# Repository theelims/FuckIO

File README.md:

# FuckIO
An opensource fucking machine, that is far superiour to anything on the market.

## Specs
* Easy to built just with a 3D-printer, screwdrivers and easy-to-source parts.
* Completely 3D-printable with easy to print parts and almost no supports. Also avoiding tight tolerances to make this accessable as possible. 
* Simple, yet verastile mechanics.
* Based on a linear position drive, not a crank mechanism.
* An 24V PWM output to drive external systems. Could be lube pumps, vibrators, etc.

## Mechanics
The mechanics is a direct derivative of an other open source project called OSSM. You can also find some informations about this build on their Discord.
https://github.com/KinkyMakers/OSSM-hardware

The motor mount is designed for a NEMA23 servo or stepper motor. Any motor fitting to this standart should work. 

### BOM
* iHSV57-30-18-36-... integrated servo motor from JMC
* 24V Power Brick Mean Well GST280A24-C6P 
* 40cm MGN12H linear rail
* 4x 605-2RS Z2 bearings
* Micro Switch
* GT2 20 Tooth Pulley for 8mm Axis and a 10mm belt
* GT2 belt with 10mm width
* Various M3 and M5 screws and nuts
* OSSM Ref Board from Research and Desire: https://shop.researchanddesire.com/collections/all/products/ossm-reference-board
* M5 Stack Remote Control from Ortlof: https://github.com/ortlof/OSSM-M5-Remote

## Control
### Firmware
The currently best firmware is the official OSSM firmware, or Ortlof's firmware for the M5 Remote https://github.com/ortlof/OSSM-M5-Remote

The firmware in the repository can only be used in conjunction with node-red.

The firmware uses the following projects:
* IotWebConf for WiFi provisioning: https://github.com/prampec/IotWebConf. Check the [end-user manual](https://github.com/prampec/IotWebConf/blob/master/doc/UsersManual.md) on how to use it.
* MQTT for communication: https://github.com/256dpi/arduino-mqtt Albeit SSL is not supported.
* My own library for generating the stroking motion: https://github.com/theelims/StrokeEngine/
* Which in turn uses https://github.com/gin66/FastAccelStepper for step generation and interfacing the servo motor.

### node-red
I've setup a node-red instance on my NAS to control FuckIO through MQTT messages. Have a look at the provided [flows.json](node-red/flows.json) to draw some inspiration from.

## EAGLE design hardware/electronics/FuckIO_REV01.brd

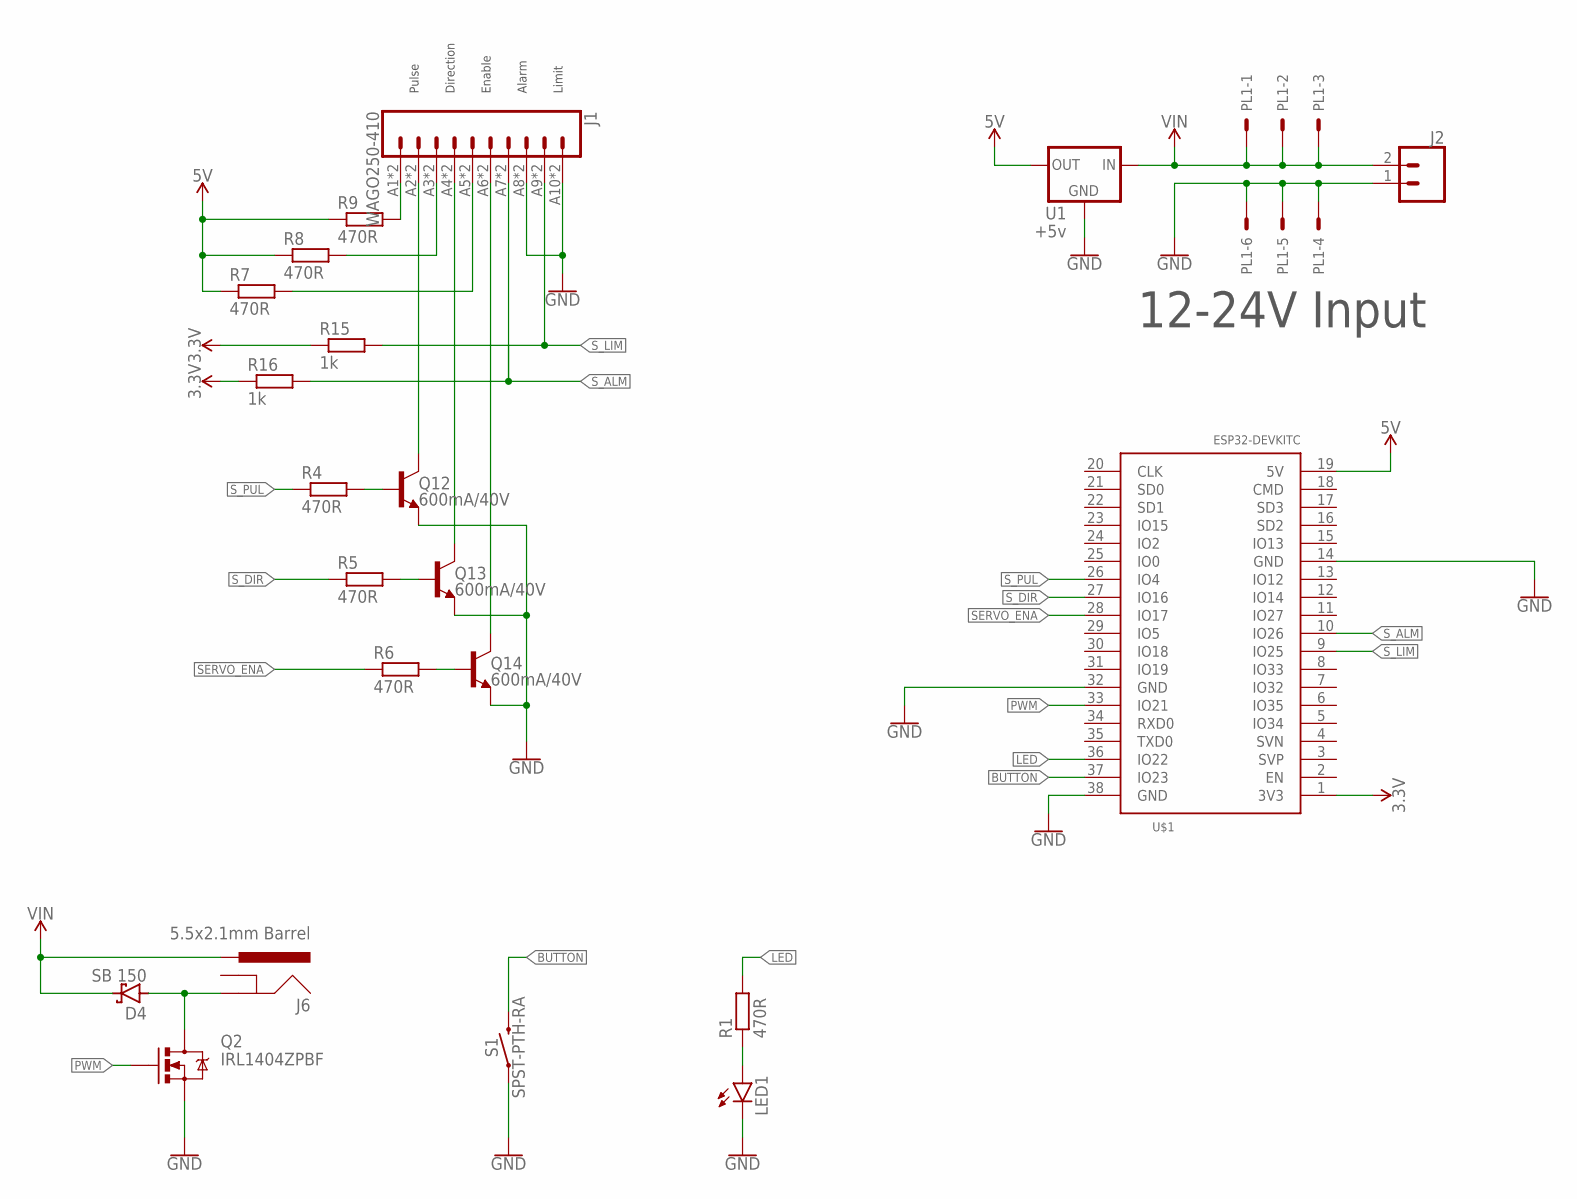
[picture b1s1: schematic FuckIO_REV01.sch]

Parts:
D4: SB 150; DIODE_DO41-10
J1: WAGO250-410; BEE_WAGO250-410
J2: CONN_025MM; SPARKFUN-CONNECTORS_SCREWTERMINAL-5MM-2
J6: 5.5x2.1mm Barrel; SPARKFUN-CONNECTORS_POWER_JACK_PTH
LED1: LED5MM
PL1: CON-MOLEX-2_555X-6H; CON-MOLEX-2_5569-6
Q2: IRL1404ZPBF; BEE_TO220-IGO
Q12, Q13, Q14: 600mA/40V; SPARKFUN-DISCRETESEMI_TO-92
R1, R4, R5, R6, R7, R8, R9: 470R; RCL_0204/5
R15, R16: 1k; RCL_0204/5
S1: SPST-PTH-RA; TACTILE_SWITCH_PTH_RIGHT_ANGLE_KIT
U1: +5v; SPARKFUN-IC-POWER_TO220-IGO
U$1: ESP32DEVKITC; ESP32-DEVKITC

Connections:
3.3V: R15.1, R16.1, U$1.1 (3V3)
5V: R7.1, R8.1, R9.1, U1.OUT, U$1.19 (5V)
BUTTON: S1.2, U$1.37 (IO23)
GND: J1.A8 (8), J1.A10 (10), J1.B8 (8), J1.B10 (10), J2.1, LED1.K (C), PL1.4, PL1.5, PL1.6, Q2.S, Q12.3 (E), Q13.3 (E), Q14.3 (E), S1.1, U1.GND, U$1.14 (GND), U$1.32 (GND), U$1.38 (GND)
LED: R1.2, U$1.36 (IO22)
unnamed: LED1.A, R1.1
unnamed: J1.A5 (5), J1.B5 (5), R7.2
unnamed: J1.A3 (3), J1.B3 (3), R8.2
unnamed: J1.A1 (1), J1.B1 (1), R9.2
unnamed: J1.A6 (6), J1.B6 (6), Q14.1 (C)
unnamed: J1.A4 (4), J1.B4 (4), Q13.1 (C)
unnamed: J1.A2 (2), J1.B2 (2), Q12.1 (C)
unnamed: Q12.2 (B), R4.2
unnamed: Q13.2 (B), R5.2
unnamed: Q14.2 (B), R6.2
unnamed: D4.A, J6.GND, Q2.D
PWM: Q2.G, U$1.33 (IO21)
SERVO_ENA: R6.1, U$1.28 (IO17)
S_ALM: J1.A7 (7), J1.B7 (7), R16.2, U$1.10 (IO26)
S_DIR: R5.1, U$1.27 (IO16)
S_LIM: J1.A9 (9), J1.B9 (9), R15.2, U$1.9 (IO25)
S_PUL: R4.1, U$1.26 (IO4)
VIN: D4.C, J2.2, J6.PWR, PL1.1, PL1.2, PL1.3, U1.IN

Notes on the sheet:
Pulse
Direction
Enable
Alarm
12-24V Input
Limit

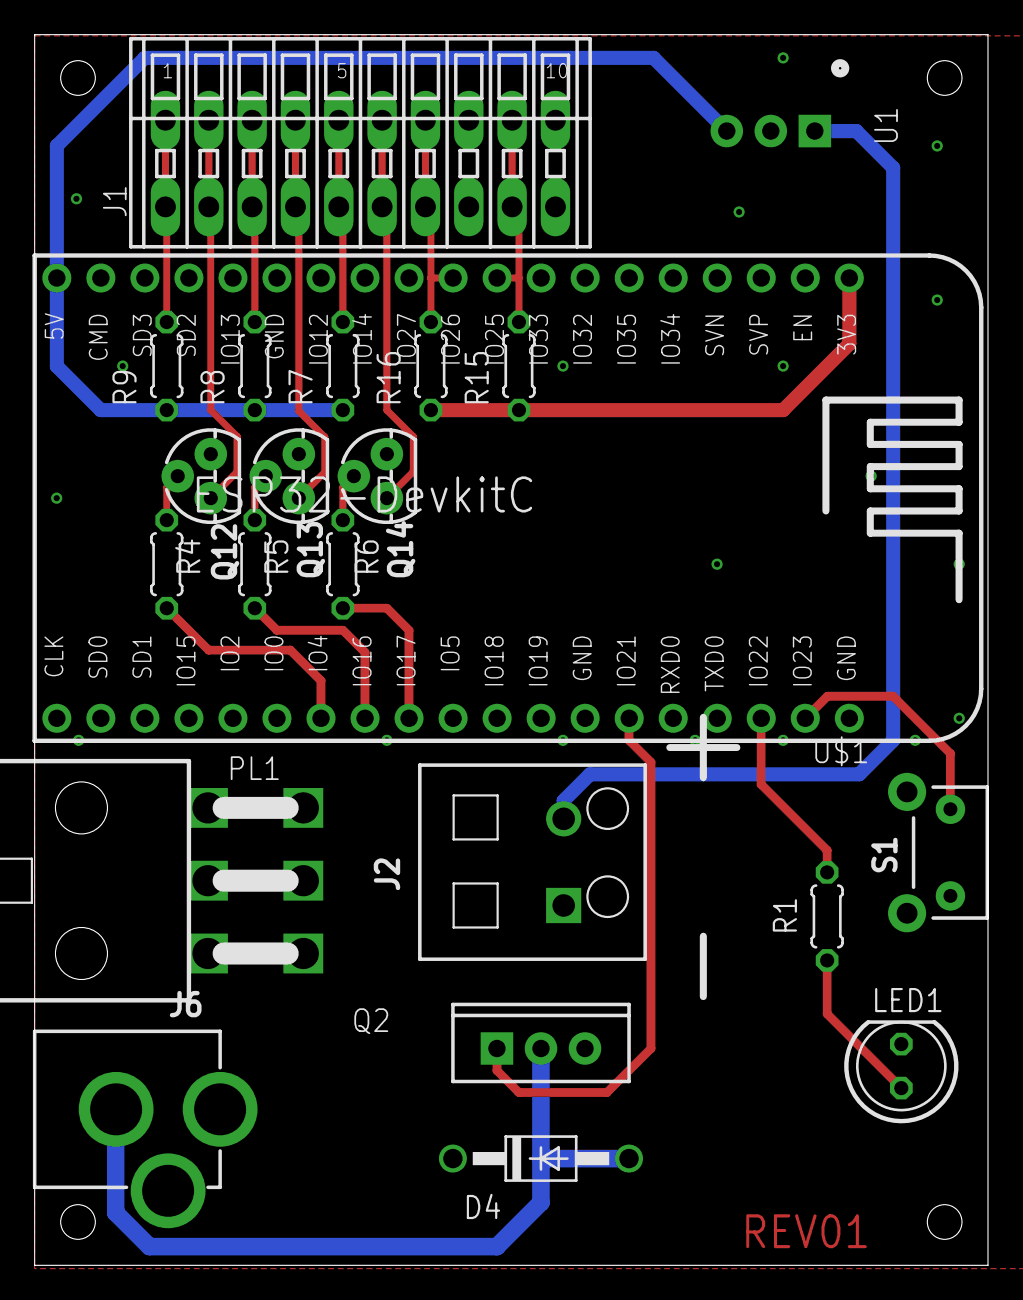
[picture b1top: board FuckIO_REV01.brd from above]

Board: 2 copper layers, 55.0 x 71.0 mm, 22 parts (0 on the bottom side), 23 nets.

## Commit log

2021-06-23 Delete PCB
    PCB was a failure and didn't work out. Going for as EPS32 solution.
2021-06-23 Delete firmware/FuckIO directory
    SAMD21 does not really work. Going for an ESP32 solution with fastaccelsteller library.
2021-06-23 Update README.md
    Recommended OSSM board and firmware.
2021-06-26 Delete FuckIO v36.step
    Obsolete
2021-06-26 Updated belt tensioner
2021-06-26 Current version with updated belt tension system
2021-08-12 Moving everything to ESP32
2021-08-12 Added API documentation
2021-08-12 moved Endstop Pin to lib
2021-08-15 Split off StrokeEngine as library
2021-08-15 Added electronics
2021-08-26 Bugfix: Stacksize Housekeeping Task
2021-08-26 Cleaning up unneeded includes
2021-09-11 Included new setup depth mode of StrokeEngine
2021-09-13 StrokeEngine API Changed
2021-11-26 Changes to reflect latest StrokeEngine Release
2021-11-26 Update of StrokeEngine
2022-01-01 Increased MQTT buffer size to accommodate more patterns
2022-01-15 Code adaptations to suite StrokeEngine v0.3.0
2023-01-05 new StrokEngine dev
2023-01-06 Support for virtual motor and ESP logging
2023-05-11 Electronics is obsolet

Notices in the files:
parts and their libraries:
SparkFun-Switches: Licensing: Creative Commons ShareAlike 4.0 International - https://creativecommons.org/licenses/by-sa/4.0
